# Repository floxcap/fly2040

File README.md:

# fly2040

RP2040 board, leds, firmware and homebrew designed to be picofly compatable.

NOTE: Using `git-subrepo` for submodules. See [git-subrepo](https://github.com/ingydotnet/git-subrepo) for usage.

## Credits
- Further credits in relevant sub-folders.
- A huge thank you to [SciresM](https://github.com/SciresM) for all of the guidance and help in getting this working.
- Also a huge thank you to [CTCaer](https://github.com/CTCaer) for all of the guidance and focus on the small details.
- Thanks to [rehius](https://github.com/rehius) for the picofly firmware which was the foundation for the fly2040 firmware.
- Thanks to [lightninjay](https://gbatemp.net/members/lightninjay.643395/) for his guide [guide](doc/PicoFlyGuideV.6.2-1.pdf) and [guide-thread](https://gbatemp.net/download/a-definitive-picofly-install-guide.37968/).

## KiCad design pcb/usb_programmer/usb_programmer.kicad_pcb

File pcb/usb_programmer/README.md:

# fly2040 USB Programmer
KiCad design for a basic programmer board.

Note - This design is currently untested.

The usb-programmer board is designed to accept the P50-E2 (shaft diameter 0.68mm) which should be soldered in
to the (programmer) board.<br><br>

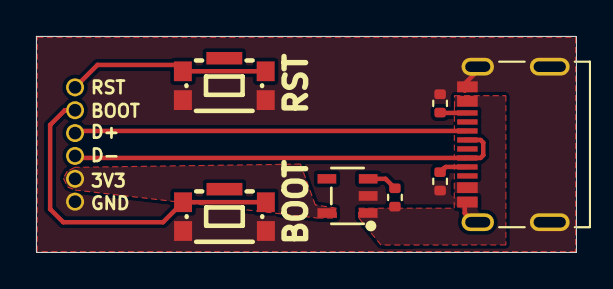
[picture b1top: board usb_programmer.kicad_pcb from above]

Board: 2 copper layers, 30.0 x 12.0 mm, 8 parts (0 on the bottom side), 10 nets.

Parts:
J1: TYPE-C-31-M-12; USB_TYPE-C
J2: Conn_01x06; ProgPinsHoles_1x06_P1.27mm
R1: 10k; R_0402_1005Metric
R2, R3: 5.1k; R_0402_1005Metric
SW1, SW3: KMR221GLFS; KEY-SMD_KMR2XXGXXX
U1: RT9080-33GJ5; TSOT-23-5_L2.9-W1.6-P0.95-LS2.8-BL

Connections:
+3V3: J2.5, U1.5 (VOUT)
BOOT: J2.2, SW1.1, SW1.2
D+: J1.A6 (D+), J1.B6 (D+), J2.3
D-: J1.A7 (D-), J1.B7 (D-), J2.4
GND: J1.A1 (GND), J1.A12 (GND), J1.S1 (SHIELD), J2.6, R2.2, R3.2, SW1.3, SW1.4, SW3.3, SW3.4, U1.2 (GND)
unnamed: J1.A5 (CC1), R3.1
unnamed: J1.B5 (CC2), R2.1
unnamed: R1.2, U1.3 (EN)
RST: J2.1, SW3.1, SW3.2
VBUS: J1.A4 (VBUS), J1.A9 (VBUS), R1.1, U1.1 (VIN)

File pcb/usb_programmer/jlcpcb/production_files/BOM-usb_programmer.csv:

Comment,Designator,Footprint,LCSC
TYPE-C-31-M-12,J1,USB_TYPE-C,C165948
10k,R1,R_0402_1005Metric,C25744
5.1k,"R2,R3",R_0402_1005Metric,C25905
KMR221GLFS,"SW1,SW3",KEY-SMD_KMR2XXGXXX,C72443
RT9080-33GJ5,U1,TSOT-23-5_L2.9-W1.6-P0.95-LS2.8-BL,C841192

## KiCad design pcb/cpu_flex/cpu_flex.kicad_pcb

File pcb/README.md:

# fly2040 pcbs
KiCad designs for a RP2040 board and supporting boards.

Note - The main board requires a 3.3V power supply when programming.<br>
The intention is to be able to program the boards with a 1.27mm pitch test clip / pogo pins.
(See: [usb_programmer](usb_programmer)).

The [fly2040_rgb](fly2040_rgb) board is the main board and has been tested and working
on V1/V2/Lite devices.

The [fly2040_leds](fly2040_leds) adds support for a flex led strip.

The [cpu_flex](cpu_flex) is untested.

## Installation
See: [guide](../doc/PicoFlyGuideV.6.2-1.pdf) or [guide-thread](https://gbatemp.net/download/a-definitive-picofly-install-guide.37968/)

The usb-programmer board is designed to accept the P50-E2 (shaft diameter 0.68mm) which should be soldered in
to the (programmer) board.

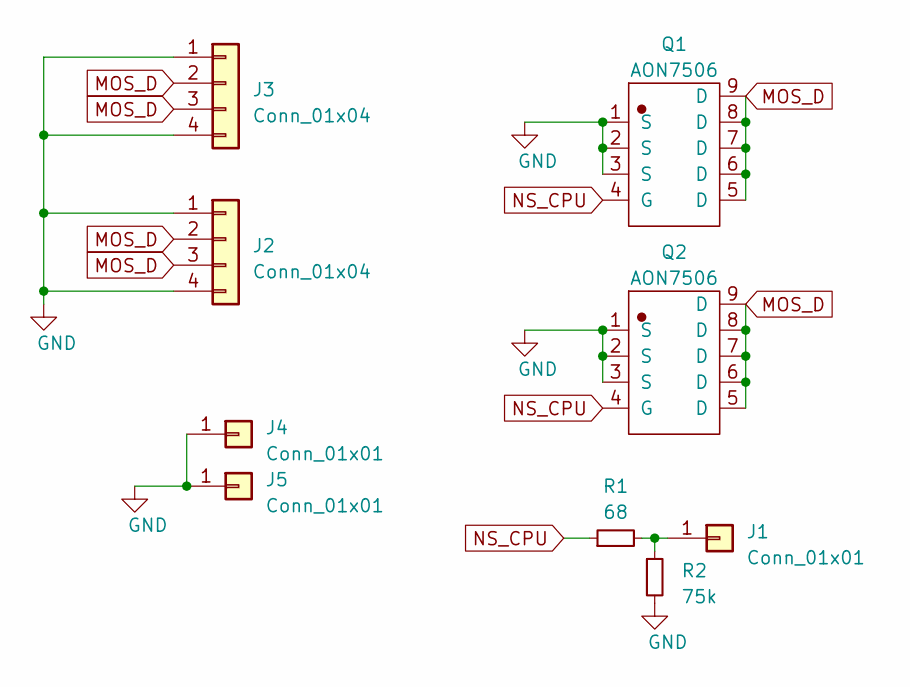
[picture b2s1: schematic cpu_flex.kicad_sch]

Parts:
J1: Conn_01x01; TH_Pads_1x1_P1.20mml
J2, J3: Conn_01x04; CPU_Pads
J4, J5: Conn_01x01; ThroughPad_2.8x1.5
Q1, Q2: AON7506; DFN-8_L3.0-W3.0-P0.65-BL
R1: 68; R_0603_1608Metric; MFGPN 0603WAF680JT5E; LCSC C27592
R2: 75k; R_0402_1005Metric; MFGPN 0402WGF7502TCE; LCSC C25798

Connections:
GND: J2.1, J2.4, J3.1, J3.4, J4.1, J5.1, Q1.1 (S), Q1.2 (S), Q1.3 (S), Q2.1 (S), Q2.2 (S), Q2.3 (S), R2.2
MOS_D: J2.2, J2.3, J3.2, J3.3, Q1.5 (D), Q1.6 (D), Q1.7 (D), Q1.8 (D), Q1.9 (D), Q2.5 (D), Q2.6 (D), Q2.7 (D), Q2.8 (D), Q2.9 (D)
NS_CPU: Q1.4 (G), Q2.4 (G), R1.1
unnamed: J1.1, R1.2, R2.1

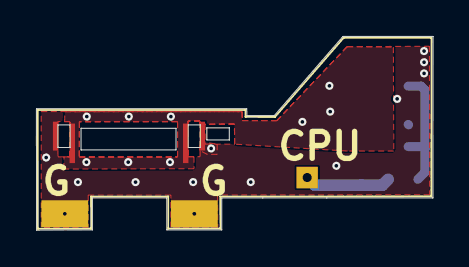
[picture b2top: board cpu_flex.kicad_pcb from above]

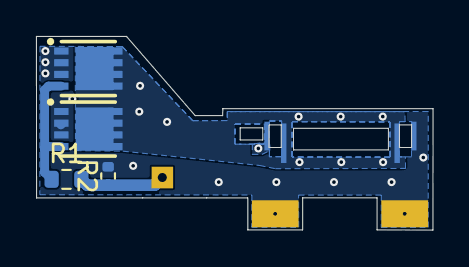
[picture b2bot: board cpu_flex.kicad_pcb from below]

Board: 2 copper layers, 22.0 x 10.8 mm, 9 parts (5 on the bottom side), 4 nets.

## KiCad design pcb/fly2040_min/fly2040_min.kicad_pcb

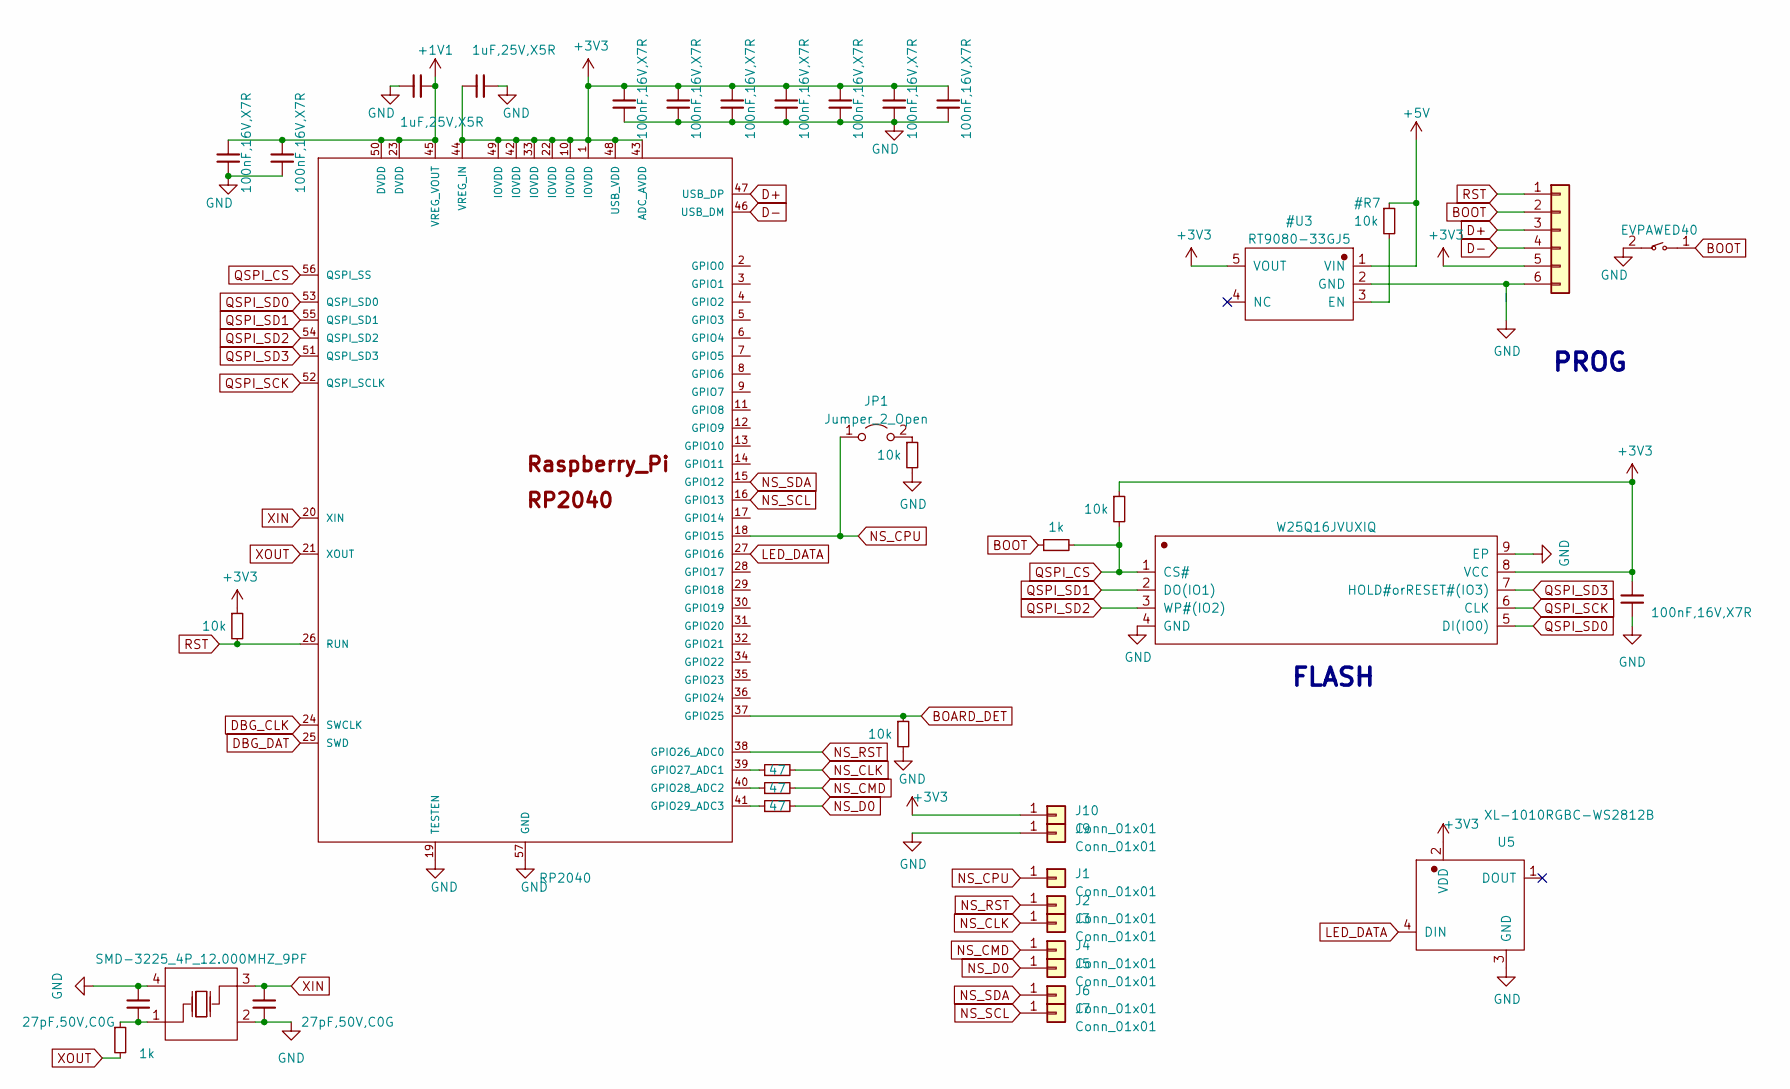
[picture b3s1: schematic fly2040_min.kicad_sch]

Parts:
C1, C3: 27pF,50V,C0G; C_0402_1005Metric; MFGPN 0402CG270J500NT; LCSC C1557
C2, C4, C7, C8, C9, C10, C11, C12, C13, C14: 100nF,16V,X7R; C_0402_1005Metric; MFGPN CL05B104KO5NNNC; LCSC C1525
C5, C6: 1uF,25V,X5R; C_0402_1005Metric; MFGPN CL05A105KA5NQNC; LCSC C52923
J1, J2, J3, J4, J5, J6, J7, J9, J10: Conn_01x01; TH_Pads_1x1_P1.20mml
J8: Conn_01x06; ProgPins_1x06_P1.27mm
JP1: Jumper_2_Open; SolderJumper-2_P1.3mm_Open_TrianglePad1.0x1.5mm_Sm
R1, R5: 1k; R_0402_1005Metric; MFGPN 0402WGF1001TCE; LCSC C11702
R2, R3, R6, R12: 10k; R_0402_1005Metric; MFGPN 0402WGF1002TCE; LCSC C25744
R9, R10, R11: 47; R_0402_1005Metric; MFGPN 0402WGF470JTCE; LCSC C25118
SW1: EVPAWED40; KEY-SMD_L3.0-W2.0-LS3.5; LCSC C2858607
U1: RP2040; LQFN-56_L7.0-W7.0-P0.4-EP; LCSC C2040
U2: W25Q16JVUXIQ; USON-8_L3.0-W2.0-P0.50-BL-EP; LCSC C2843335
U5: XL-1010RGBC-WS2812B; LED-SMD_4P-L1.0-W1.0-TL_XL-1010RGBC-WS2812B; LCSC C5349953
X1: SMD-3225_4P_12.000MHZ_9PF; OSC-SMD_4P-L3.2-W2.5-BL; LCSC C362368

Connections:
+1V1: C2.1, C4.1, C5.1, U1.23 (DVDD), U1.45 (VREG_VOUT), U1.50 (DVDD)
BOARD_DET: R3.1, U1.37 (GPIO25)
BOOT: J8.2, R5.1, SW1.1
D+: J8.3, U1.47 (USB_DP)
D-: J8.4, U1.46 (USB_DM)
DBG_CLK: U1.24 (SWCLK)
DBG_DAT: U1.25 (SWD)
LED_DATA: U1.27 (GPIO16), U5.4 (DIN)
NS_CLK: J3.1, R9.2
NS_CMD: J4.1, R10.2
NS_CPU: J1.1, JP1.1 (A), U1.18 (GPIO15)
NS_D0: J5.1, R11.2
NS_RST: J2.1, U1.38 (GPIO26_ADC0)
NS_SCL: J7.1, U1.16 (GPIO13)
NS_SDA: J6.1, U1.15 (GPIO12)
unnamed: JP1.2 (B), R12.1
unnamed: R9.1, U1.39 (GPIO27_ADC1)
unnamed: R10.1, U1.40 (GPIO28_ADC2)
unnamed: R11.1, U1.41 (GPIO29_ADC3)
unnamed: C1.2, R1.1, X1.1 (OSC1)
QSPI_CS: R5.2, R6.2, U1.56 (QSPI_SS), U2.1 (CS#)
QSPI_SCK: U1.52 (QSPI_SCLK), U2.6 (CLK)
QSPI_SD0: U1.53 (QSPI_SD0), U2.5 (DI(IO0))
QSPI_SD1: U1.55 (QSPI_SD1), U2.2 (DO(IO1))
QSPI_SD2: U1.54 (QSPI_SD2), U2.3 (WP#(IO2))
QSPI_SD3: U1.51 (QSPI_SD3), U2.7 (HOLD#orRESET#(IO3))
RST: J8.1, R2.2, U1.26 (RUN)
XIN: C3.1, U1.20 (XIN), X1.3 (OSC2)
XOUT: R1.2, U1.21 (XOUT)

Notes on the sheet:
PROG
FLASH

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
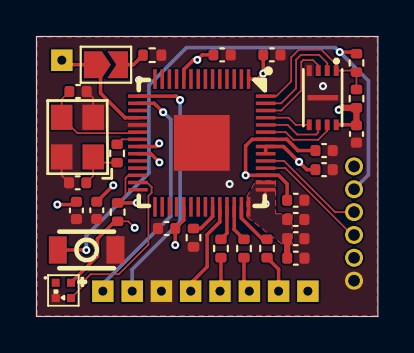
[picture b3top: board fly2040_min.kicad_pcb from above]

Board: 4 copper layers, 19.0 x 15.6 mm, 39 parts (0 on the bottom side), 29 nets.

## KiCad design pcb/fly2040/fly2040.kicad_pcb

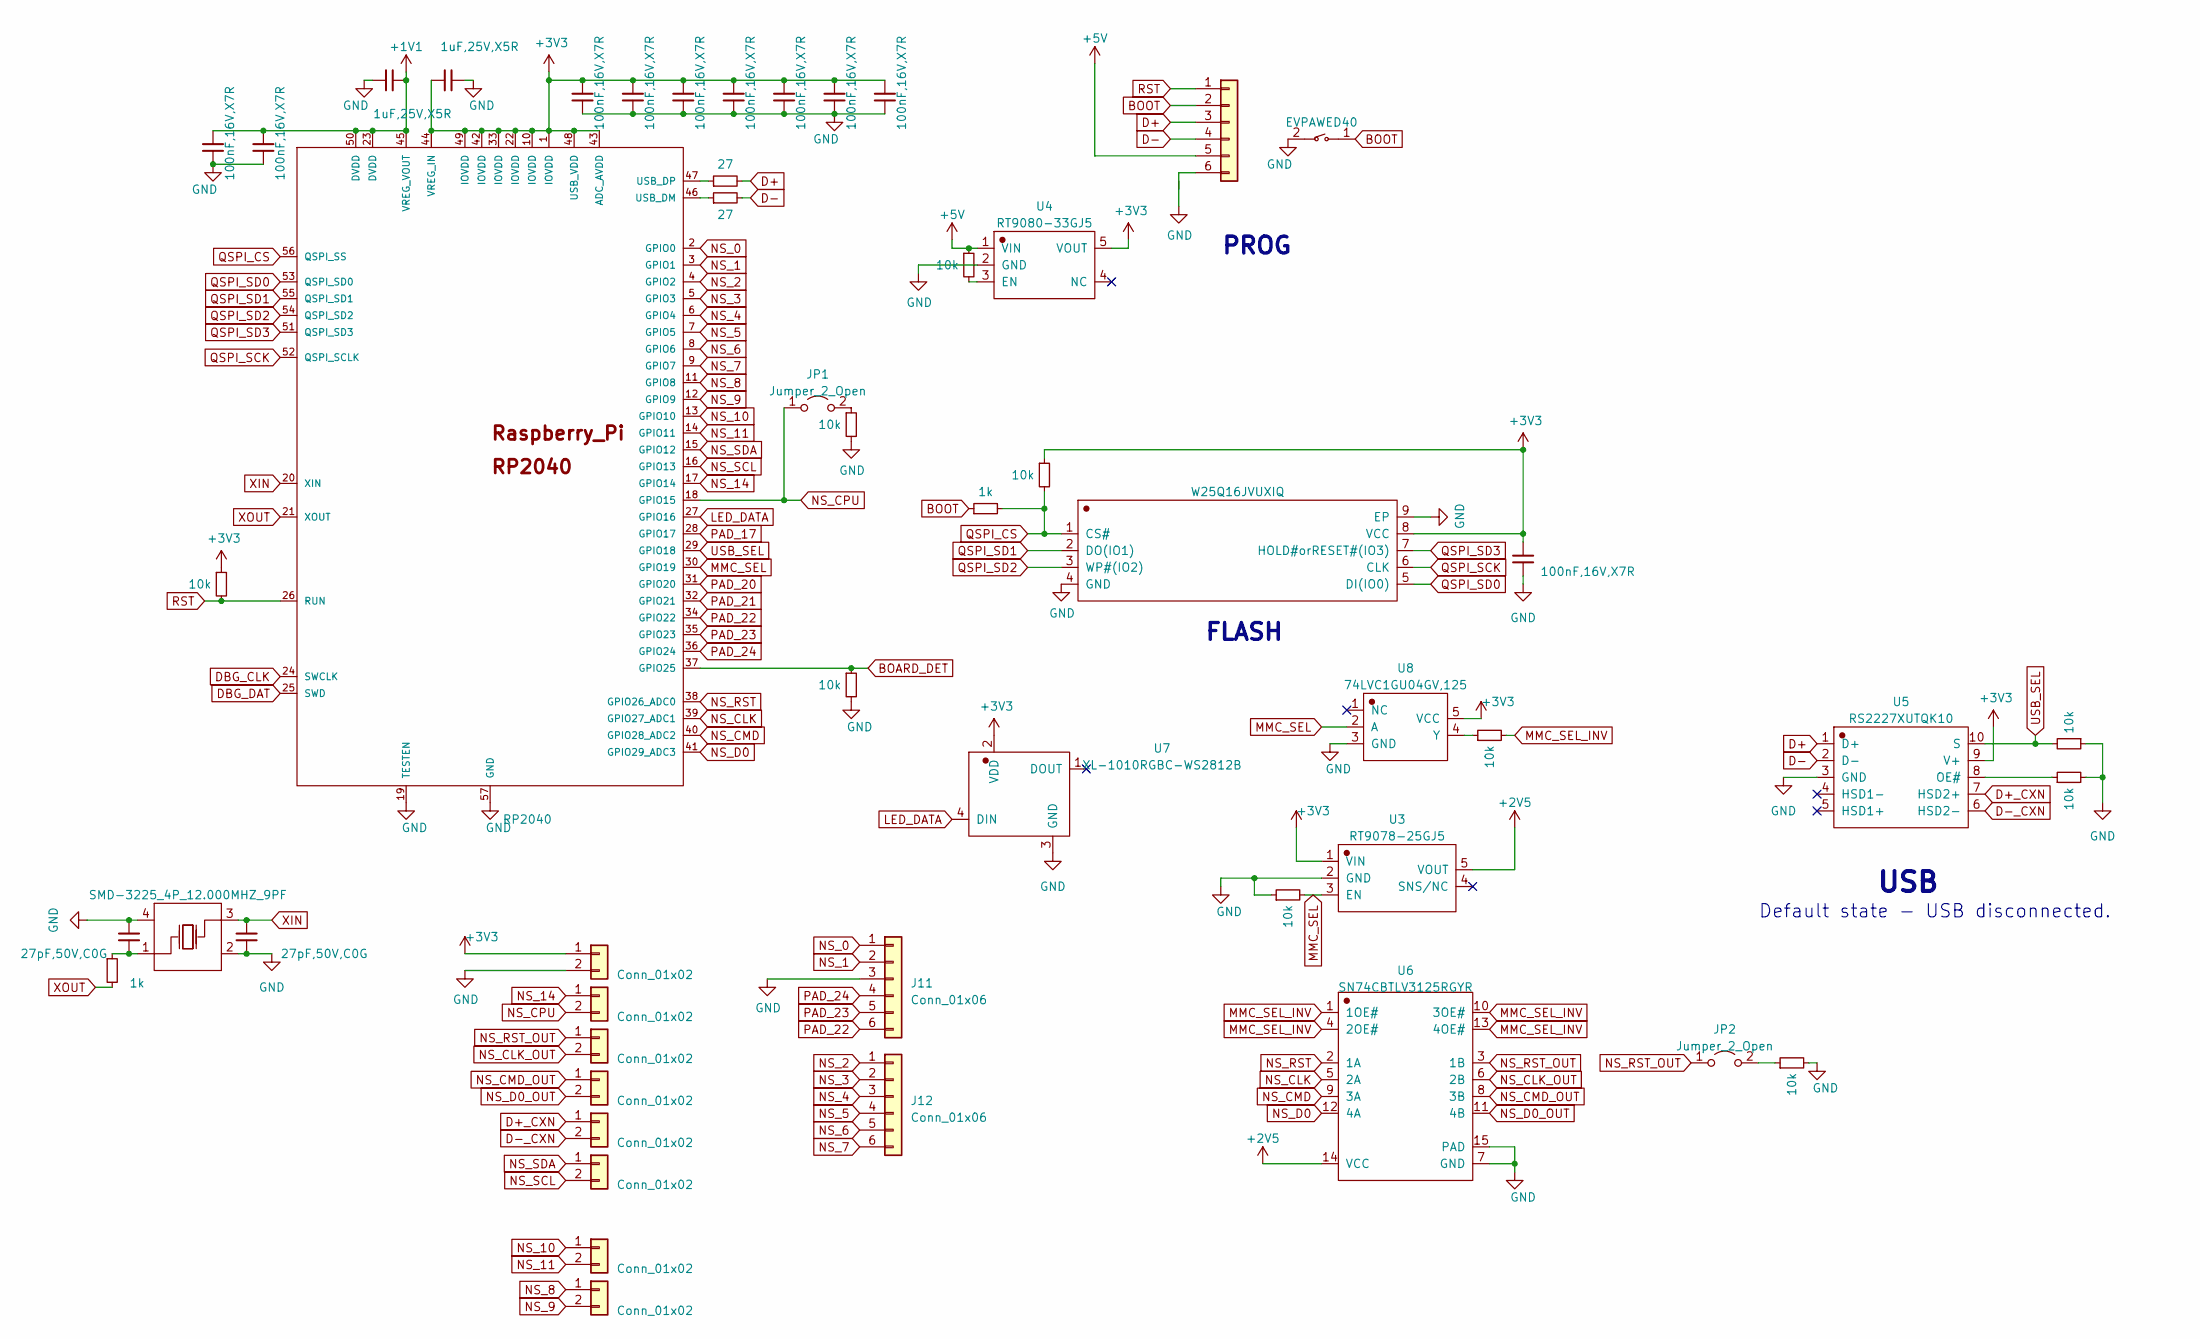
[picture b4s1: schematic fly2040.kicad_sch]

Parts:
C1, C3: 27pF,50V,C0G; C_0402_1005Metric; MFGPN 0402CG270J500NT; LCSC C1557
C2, C4, C7, C8, C9, C10, C11, C12, C13, C14: 100nF,16V,X7R; C_0402_1005Metric; MFGPN CL05B104KO5NNNC; LCSC C1525
C5, C6: 1uF,25V,X5R; C_0402_1005Metric; MFGPN CL05A105KA5NQNC; LCSC C52923
J1, J2, J3, J4, J5, J6, J9, J10: Conn_01x02; TH_Pads_1x02_P1.50mml
J8: Conn_01x06; ProgPins_1x06_P1.27mm
J11, J12: Conn_01x06; Pad_6Pin
JP1, JP2: Jumper_2_Open; SolderJumper-2_P1.3mm_Open_TrianglePad1.0x1.5mm_Sm
R1, R5: 1k; R_0402_1005Metric; MFGPN 0402WGF1001TCE; LCSC C11702
R2, R6, R7, R8, R9, R12, R13, R14, R15, R16: 10k; R_0402_1005Metric; MFGPN 0402WGF1002TCE; LCSC C25744
R3, R4: 27; R_0402_1005Metric; MFGPN 0402WGF270JTCE; LCSC C25100
SW1: EVPAWED40; KEY-SMD_L3.0-W2.0-LS3.5; LCSC C2858607
U1: RP2040; LQFN-56_L7.0-W7.0-P0.4-EP; LCSC C2040
U2: W25Q16JVUXIQ; USON-8_L3.0-W2.0-P0.50-BL-EP; LCSC C2843335
U3: RT9078-25GJ5; TSOT-23-5_L2.9-W1.6-P0.95-LS2.8-BL; LCSC C965901
U4: RT9080-33GJ5; TSOT-23-5_L2.9-W1.6-P0.95-LS2.8-BL; LCSC C841192
U5: RS2227XUTQK10; WQFN-10_L1.8-W1.4-P0.40-BL; LCSC C783419
U6: SN74CBTLV3125RGYR; VQFN-14_L3.5-W3.5-P0.50-BL-EP; LCSC C133940
U7: XL-1010RGBC-WS2812B; LED-SMD_4P-L1.0-W1.0-TL_XL-1010RGBC-WS2812B; LCSC C5349953
U8: 74LVC1GU04GV,125; SC-74A-5_L2.9-W1.6-P0.95-LS2.8-BL; LCSC C548470
X1: SMD-3225_4P_12.000MHZ_9PF; OSC-SMD_4P-L3.2-W2.5-BL; LCSC C362368

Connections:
+1V1: C2.1, C4.1, C5.1, U1.23 (DVDD), U1.45 (VREG_VOUT), U1.50 (DVDD)
+2V5: U3.5 (VOUT), U6.14 (VCC)
+3V3: C6.2, C7.1, C8.1, C9.1, C10.1, C11.1, C12.1, C13.1, C14.1, J1.1, R2.1, R6.1, U1.1 (IOVDD), U1.10 (IOVDD), U1.22 (IOVDD), U1.33 (IOVDD), U1.42 (IOVDD), U1.43 (ADC_AVDD), U1.44 (VREG_IN), U1.48 (USB_VDD), U1.49 (IOVDD), U2.8 (VCC), U3.1 (VIN), U4.5 (VOUT), U5.9 (V+), U7.2 (VDD), U8.5 (VCC)
+5V: J8.5, R8.1, U4.1 (VIN)
BOARD_DET: R7.1, U1.37 (GPIO25)
BOOT: J8.2, R5.1, SW1.1
D+: J8.3, R3.2, U5.1 (D+)
D+_CXN: J5.1, U5.7 (HSD2+)
D-: J8.4, R4.2, U5.2 (D-)
D-_CXN: J5.2, U5.6 (HSD2-)
DBG_CLK: U1.24 (SWCLK)
DBG_DAT: U1.25 (SWD)
GND: C1.1, C2.2, C3.2, C4.2, C5.2, C6.1, C7.2, C8.2, C9.2, C10.2, C11.2, C12.2, C13.2, C14.2, J1.2, J8.6, J11.3, R7.2, R9.2, R12.2, R13.1, R14.2, R15.1, SW1.2, U1.19 (TESTEN), U1.57 (GND), U2.4 (GND), U2.9 (EP), U3.2 (GND), U4.2 (GND), U5.3 (GND), U6.7 (GND), U6.15 (PAD), U7.3 (GND), U8.3 (GND), X1.2, X1.4
LED_DATA: U1.27 (GPIO16), U7.4 (DIN)
MMC_SEL: R15.2, U1.30 (GPIO19), U3.3 (EN), U8.2 (A)
MMC_SEL_INV: R16.2, U6.1 (1OE#), U6.4 (2OE#), U6.10 (3OE#), U6.13 (4OE#)
NS_0: J11.1, U1.2 (GPIO0)
NS_1: J11.2, U1.3 (GPIO1)
NS_2: J12.1, U1.4 (GPIO2)
NS_3: J12.2, U1.5 (GPIO3)
NS_4: J12.3, U1.6 (GPIO4)
NS_5: J12.4, U1.7 (GPIO5)
NS_6: J12.5, U1.8 (GPIO6)
NS_7: J12.6, U1.9 (GPIO7)
NS_8: J10.1, U1.11 (GPIO8)
NS_9: J10.2, U1.12 (GPIO9)
NS_10: J9.1, U1.13 (GPIO10)
NS_11: J9.2, U1.14 (GPIO11)
NS_14: J2.1, U1.17 (GPIO14)
NS_CLK: U1.39 (GPIO27_ADC1), U6.5 (2A)
NS_CLK_OUT: J3.2, U6.6 (2B)
NS_CMD: U1.40 (GPIO28_ADC2), U6.9 (3A)
NS_CMD_OUT: J4.1, U6.8 (3B)
NS_CPU: J2.2, JP1.1 (A), U1.18 (GPIO15)
NS_D0: U1.41 (GPIO29_ADC3), U6.12 (4A)
NS_D0_OUT: J4.2, U6.11 (4B)
NS_RST: U1.38 (GPIO26_ADC0), U6.2 (1A)
NS_RST_OUT: J3.1, JP2.1 (A), U6.3 (1B)
NS_SCL: J6.2, U1.16 (GPIO13)
NS_SDA: J6.1, U1.15 (GPIO12)
unnamed: JP1.2 (B), R12.1
unnamed: JP2.2 (B), R9.1
unnamed: R4.1, U1.46 (USB_DM)
unnamed: R3.1, U1.47 (USB_DP)
unnamed: R8.2, U4.3 (EN)
unnamed: R14.1, U5.8 (OE#)
unnamed: R16.1, U8.4 (Y)
unnamed: C1.2, R1.1, X1.1 (OSC1)
PAD_17: U1.28 (GPIO17)
PAD_20: U1.31 (GPIO20)
PAD_21: U1.32 (GPIO21)
PAD_22: J11.6, U1.34 (GPIO22)
PAD_23: J11.5, U1.35 (GPIO23)
PAD_24: J11.4, U1.36 (GPIO24)
QSPI_CS: R5.2, R6.2, U1.56 (QSPI_SS), U2.1 (CS#)
QSPI_SCK: U1.52 (QSPI_SCLK), U2.6 (CLK)
QSPI_SD0: U1.53 (QSPI_SD0), U2.5 (DI(IO0))
QSPI_SD1: U1.55 (QSPI_SD1), U2.2 (DO(IO1))
QSPI_SD2: U1.54 (QSPI_SD2), U2.3 (WP#(IO2))
QSPI_SD3: U1.51 (QSPI_SD3), U2.7 (HOLD#orRESET#(IO3))
RST: J8.1, R2.2, U1.26 (RUN)
USB_SEL: R13.2, U1.29 (GPIO18), U5.10 (S)
XIN: C3.1, U1.20 (XIN), X1.3 (OSC2)
XOUT: R1.2, U1.21 (XOUT)

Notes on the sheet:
USB
PROG
Default state - USB disconnected.
FLASH

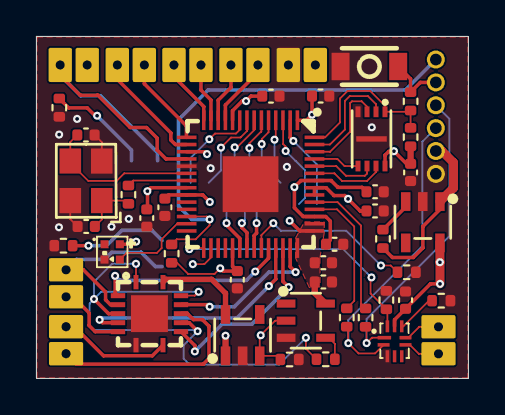
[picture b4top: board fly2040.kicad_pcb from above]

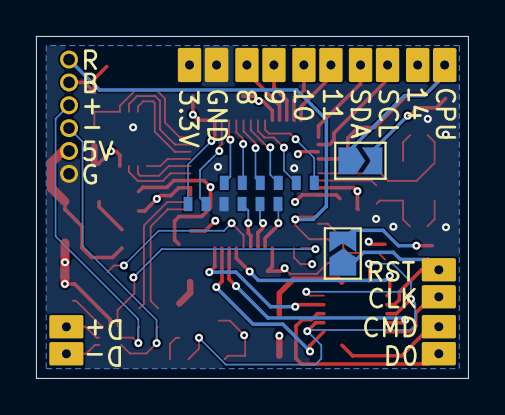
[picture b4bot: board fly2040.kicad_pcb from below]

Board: 4 copper layers, 24.0 x 19.0 mm, 51 parts (4 on the bottom side), 59 nets.

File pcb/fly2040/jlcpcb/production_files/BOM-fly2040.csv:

Comment,Designator,Footprint,LCSC
1k,"R1,R5",R_0402_1005Metric,C11702
SN74CBTLV3125RGYR,U6,VQFN-14_L3.5-W3.5-P0.50-BL-EP,C133940
"100nF,16V,X7R ","C10,C11,C12,C13,C14,C2,C4,C7,C8,C9",C_0402_1005Metric,C1525
"27pF,50V,C0G ","C1,C3",C_0402_1005Metric,C1557
RP2040,U1,LQFN-56_L7.0-W7.0-P0.4-EP,C2040
27,"R3,R4",R_0402_1005Metric,C25100
10k,"R12,R13,R14,R15,R16,R2,R6,R7,R8,R9",R_0402_1005Metric,C25744
W25Q16JVUXIQ,U2,USON-8_L3.0-W2.0-P0.50-BL-EP,C2843335
EVPAWED40,SW1,KEY-SMD_L3.0-W2.0-LS3.5,C2858607
SMD-3225_4P_12.000MHZ_9PF,X1,OSC-SMD_4P-L3.2-W2.5-BL,C362368
"1uF,25V,X5R ","C5,C6",C_0402_1005Metric,C52923
XL-1010RGBC-WS2812B,U7,LED-SMD_4P-L1.0-W1.0-TL_XL-1010RGBC-WS2812B,C5349953
"74LVC1GU04GV,125",U8,SC-74A-5_L2.9-W1.6-P0.95-LS2.8-BL,C548470
RS2227XUTQK10,U5,WQFN-10_L1.8-W1.4-P0.40-BL,C783419
RT9080-33GJ5,U4,TSOT-23-5_L2.9-W1.6-P0.95-LS2.8-BL,C841192
RT9078-25GJ5,U3,TSOT-23-5_L2.9-W1.6-P0.95-LS2.8-BL,C965901

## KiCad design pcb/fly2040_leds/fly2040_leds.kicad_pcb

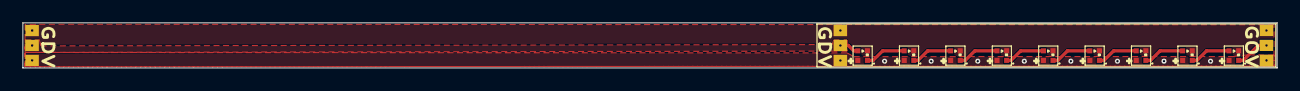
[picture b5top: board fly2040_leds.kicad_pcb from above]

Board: 2 copper layers, 111.2 x 4.0 mm, 18 parts (0 on the bottom side), 12 nets.

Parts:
J1, J2, J3, J4, J5, J6, J7, J8, J9: Conn_01x01; TH_Pads_1.2x1_P1.20mml
U1, U2, U3, U4, U5, U6, U7, U8, U9: XL-1010RGBC-WS2812B; LED-SMD_4P-L1.0-W1.0-TL_XL-1010RGBC-WS2812B

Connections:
+3V3: J1.1, J5.1, J7.1, U1.2 (VDD), U2.2 (VDD), U3.2 (VDD), U4.2 (VDD), U5.2 (VDD), U6.2 (VDD), U7.2 (VDD), U8.2 (VDD), U9.2 (VDD)
GND: J2.1, J6.1, J8.1, U1.3 (GND), U2.3 (GND), U3.3 (GND), U4.3 (GND), U5.3 (GND), U6.3 (GND), U7.3 (GND), U8.3 (GND), U9.3 (GND)
LED_DATA: J3.1, J9.1, U1.4 (DIN)
LED_OUT: J4.1, U9.1 (DOUT)
unnamed: U1.1 (DOUT), U2.4 (DIN)
unnamed: U2.1 (DOUT), U3.4 (DIN)
unnamed: U3.1 (DOUT), U4.4 (DIN)
unnamed: U4.1 (DOUT), U5.4 (DIN)
unnamed: U5.1 (DOUT), U6.4 (DIN)
unnamed: U6.1 (DOUT), U7.4 (DIN)
unnamed: U7.1 (DOUT), U8.4 (DIN)
unnamed: U8.1 (DOUT), U9.4 (DIN)

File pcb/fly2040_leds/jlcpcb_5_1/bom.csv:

Comment,Designator,Footprint,LCSC
XL-1010RGBC-WS2812B,"U1,U2,U3,U4,U5,U6,U7,U8,U9",kicad_lceda:LED-SMD_4P-L1.0-W1.0-TL_XL-1010RGBC-WS2812B,C5349953

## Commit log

2023-05-22 Added more outputs. Improved board layout for panel. Added panel files
2023-05-24 Add minimal board design.
2023-05-24 Add Images.
2023-05-27 Added tiny double sided (ds) board.
2023-05-29 Fix gitignore and push production files
2023-06-02 Updated main board with bus isolation ICs
2023-06-03 Minor fixes to min board to prep for production run.
2023-06-18 Add WIP CPU flex design.
2023-07-07 Add pogo-pins programmer board
2023-07-07 Add pogo info.
2023-08-11 Added new board, leds, apps, firmware
2023-08-11 Add dist
2023-08-12 git subrepo clone https://github.com/wren-lang/wren.git firmware/wren
    subrepo:
    subdir: "firmware/wren"
    merged: "c2a75f1e"
    upstream:
    origin: "https://github.com/wren-lang/wren.git"
    branch: "main"
2023-08-14 WIP - remove exceptions & add wren
2023-08-14 git subrepo clone https://github.com/floxcap/pico-littlefs-lib.git firmware/usk/pico-littlefs-lib
    subrepo:
    subdir: "firmware/usk/pico-littlefs-lib"
    merged: "d7b9d345"
    upstream:
    origin: "https://github.com/floxcap/pico-littlefs-lib.git"
    branch: "master"
2023-08-14 WIP - migrate to CBOR
2023-08-14 git subrepo clone (merge) https://github.com/bergzand/NanoCBOR.git firmware/usk/NanoCBOR
    subrepo:
    subdir: "firmware/usk/NanoCBOR"
    merged: "1bc78970"
    upstream:
    origin: "https://github.com/bergzand/NanoCBOR.git"
    branch: "master"
2023-08-27 WIP wren
2023-08-27 Update docs
